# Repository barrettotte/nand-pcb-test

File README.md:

# nand-pcb-test

Homemade PCB test using a CNC router.

Hopefully this is useful to someone else wanting a single place to see the whole CNC PCB building process.
These notes assume you have a basic understanding of Kicad and Candle (grblcontrol).

## Why?

There are plenty of companies that offer cheap PCB manufacturing, but I'm impatient and bad at designing things correctly on the first try.
Imagine ordering a PCB, waiting a few days, and figuring out you messed up your design.
Manufacturing with a CNC router helps to eliminate waiting time between idea and implementation.

Alternatively, plenty of people use the chemical etching process (example: thermal transfer paper and ferric chloride) to build their PCBs.
I just don't have a good workspace to mess with nasty chemicals, so the CNC approach is more doable for me.
Maybe I'll also add a chemical etching bonus section in the future.

For 2+ sided PCBs, it would be worth ordering from a company. Double-sided PCBs are possible, but I have not attempted this yet.
I also haven't tried designs with SMD components yet, so that may also be a pain point that warrants ordering PCBs from a company.

## Equipment

- [Genmitsu 3020-PRO MAX V2 CNC Router](https://www.sainsmart.com/collections/new-genmitsu-collection/products/3020-pro-max-v2)
  - [3040 Y-Axis Extension Kit](https://www.sainsmart.com/collections/genmitsu-cnc-replacement-upgrade-parts/products/3020-yaxis-extension-kit) (optional)
- [FR-4 Copper Clad PCB Laminate Board, Single Side, 4 x 2.7 inch (10 piece)](https://www.amazon.com/dp/B01MCVLDDZ)
- Bits
  - [0.5mm PCB End Mill Bit](https://www.amazon.com/gp/product/B073RJ3SYZ)
  - [0.8mm PCB Drill Bit](https://www.amazon.com/gp/product/B091FD44Y3)
  - [2.5mm End Mill Bit](https://www.amazon.com/gp/product/B07P84V888)
  - [Assorted PCB Drill Bit Set](https://www.amazon.com/gp/product/B08M5PLF48)
- [Mini Dry Iron](https://www.amazon.com/gp/product/B09YXVWSTQ)
- [Thermal Transfer Paper](https://www.amazon.com/gp/product/B07GLGL2CX)
- [Monochrome Laser Printer](https://www.amazon.com/gp/product/B00NQ1CLTI)
- [Mini Drill Press](https://www.amazon.com/gp/product/B0BKZRD2P7)

## Build Process

### Circuit Design and Prototyping

- Design circuit in Kicad Schematic Editor
- Breadboard implementation
- Protoboard implementation (optional)
- Kicad Schematic Editor
  - Inspect > Electrical Rules Checker
  - Tools > Annotate Schematic
  - Tools > Assign Footprints
  - File > Plot > PDF, Plot All Pages

### PCB Design

- Open Kicad PCB Editor (or from Kicad Schematic Editor: Tools > Update PCB From Schematic)
- Generally only use back copper and front silkscreen
- Rearrange rats nest of components to eliminate overlap
- Set design rules (File > Board Setup)
  - Minimum clearance: 0.5mm
  - Minimum track width: 0.5mm
  - Copper to hole clearance: 0.5mm
  - Copper to edge clearance: 0.5mm
  - Minimum through hole: 0.7mm
  - Hole to hole clearance: 0.5mm
- Route tracks on `B.Cu` (back copper) layer. Ignore ground pins, will be filled later
- Select `Edge.Cuts` layer, draw a rectangle to trace board boundary, thickness 1mm
- Select `B.Cu` layer and add fill for ground
- Right click fill edge, Zones > Fill Zone
- Add orthogonal dimensions to `User.Drawings` layer to double check board width/height
- Place origin at top left of board
- Run Design Rules Checker
- If exporting `F.Silkscreen`, I recommend setting text thickness to 0.1mm 
- Export Gerber files (File > Plot)
  - Check Use drill/place file origin
  - Export `B.Cu`, `Edge.Cuts` (used in router step)
  - Export `B.Mask` (used in solder masking step) as PDF
  - Generate Drill Files (`*-NPTH.drl` and `*-PTH.drl`)
    - Drill Origin = Drill/place file origin
    - Drill Units = Millimeters
- Print (File > Print) `F.Silkscreen` and `F.Mask` layers to PDF (used in silkscreen step)
  - Verify Print One Page Per Layer is unchecked
  - Scale 1:1
  - Select Print Mirrored

### Bits

Refer to bits listed in Equipment section above.

- Isolation routing: 0.5mm pcb milling bit
- Holes: 0.8mm drill bit
- Edge cut: 2.5mm end mill bit

I know a lot of people seem to recommend v-bits, but I found them to cut too
inconsistent to quickly throw together boards. 

I did manage to get a couple boards cut with a 0.1mm 60deg bit after manually offsetting my heightmap by 0.05 increments, but I could not replicate this every time. 
Switching to the pcb milling bit removed ~5-10 minutes of manual adjustment.

### Computer Aided Manufacturing (CAM)

- Launch FlatCAM
- Load `B.Cu` and `Edge.Cuts` gerber files (File > Open Gerber)
- Add drill files (`*.drl`) (File > Open Excellon)
  - Note: Ignore "No geometry found in file" error if no NPTH holes needed
- Options tab
  - Set units to mm
- Mirror on y-axis since we're cutting the back copper
  - Tool > Double-Sided PCB Tool
  - Mirror `B.Cu` and `*.drl` files on y-axis using Point/Box
- Select `*-B_Cu.gbr`
  - Isolation Routing section
  - Tool dia: 0.45 (note: 0.05 less than clearance set in Kicad)
  - Width (# passes): 2
  - Pass overlap: 0.10
  - Combine Passes: yes
  - Click Generate Geometry
- Select `*-B_Cu.gbr_iso`
  - Create CNC Job section
  - Cut Z: -0.015
  - Travel Z: 2
  - Feed Rate: 85.0
  - Tool dia: 0.45 (note: 0.05 less than clearance set in Kicad)
  - Spindle speed: 10000
  - Multi-Depth: yes
  - Depth/Pass: 0.08
  - Click Generate
- Select `*-B_Cu.gbr_iso_cnc`, export G-Code to `B_Cu.nc`
- Select `*-PTH.drl`
  - If too many sizes of drills, go back to Kicad and change hole sizes of individual components (we can always redrill by hand later if holes too small)
  - Create CNC Job section
  - Cut Z: -2
  - Travel Z: 2
  - Feed Rate: 100.0
  - Tool Change: no (unless using multiple drill sizes)
  - Spindle Speed: 10000
  - Click Generate
- Select `*-PTH.drl_cnc`, set tool dia to 0.8, export G-Code to `PTH.drl.nc`
- Select `*.Edge_Cuts.gbr`
  - Board cutout section
  - Tool dia: 2.5
  - Margin: 0.1
  - Gap size: 1.0
  - Gaps: 4
  - Click Generate Geometry
- Select `*-Edge_Cuts.gbr_cutout`
  - Create CNC Job section
  - Cut Z: -2
  - Travel Z: 2.0
  - Feed Rate: 50.0
  - Tool dia: 2.5
  - Spindle speed: 10000
  - Multi-Depth: yes
  - Depth/pass: 0.25
  - Click Generate
- Select `*-Edge_Cuts.gbr_cutout_cnc`, export G-Code to `Edge_Cuts.nc`

### Preparing Silkscreen

- Open `F.Silkscreen` PDF in Inkscape (to remove blank space of PDF document)
  - Select silkscreen components, export
  - Export Selection tab, Export Selected Only, 300.0 DPI, SVG

### CNC Routing

Refer to bits in "Computer Aided Manufacturing (CAM)" section

To secure the PCB to the bed, 
I used 3D printed M6 Plate Clamps from https://www.printables.com/model/250450-enhancements-for-sainsmartgenmitsu-3020-pro-max-cn/files. 
Alternatively, I saw a lot of people using carpet tape.

Probe setup using aluminum tape and z-probe that came with CNC router.

- Jog machine to upper left corner, z probe, zero XY
- Height map
  - Load nc file, click auto
  - Zero XYZ, set bit at origin
  - Probe grid, set to be ~10mm apart
  - Interpolation grid: 20, 20
  - zt = 1.0, zb = -1.0
  - Click Probe
  - Save as `height.map`
  - Click edit mode to leave edit mode
  - Verify use heightmap is checked
- Remove probes
- Load `B.Cu.nc`
- Swap to drill bit, re-zero Z
- Load `PTH.drl.nc`
- Swap to edge cut bit, re-zero Z
- Load `Edge_Cuts.nc`

### Silkscreen

- Load thermal transfer paper into printer
- Print `F.Silkscreen` SVG onto thermal transfer paper (smooth side up)
  - Ensure scale is 100%
- Tape thermal paper to front of PCB (toner side down)
- Use highest setting of dry iron to heat evenly for 2-3 minutes
- Apply polycrylic to preserve silkscreen

### Final Steps

- Use mini drill press to adjust any holes for larger through hole parts
- Use 400-600 grit sandpaper and/or steel wool to remove any small burrs on back copper
- File down tabs on sides of PCB
- Clean off with a bit of isopropyl alcohol
- Use multimeter to check all tracks for shorts
- Solder components
- Clean off any flux with isopropyl

## Archive

I tried to do a couple different steps that I hope to try again in the future.
I left my notes in [archive/](archive/).

## References

- [Candle](https://github.com/trasz/grblControl)
- [FlatCAM](http://flatcam.org/)
- [GCODE Reference](https://marlinfw.org/meta/gcode/)
- Youtube
  - [Homemade custom PCB guide using free KiCAD software; Teaching Tech](https://www.youtube.com/watch?v=NgDXPWaA5Ic)
  - [Homemade PCB using thermal transfer paper](https://www.youtube.com/watch?v=aemG_4sDz_Q)
  - [Intro to Kicad; Shawn Hymel](https://www.youtube.com/playlist?list=PL3bNyZYHcRSUhUXUt51W6nKvxx2ORvUQB)
  - [Machining a PCB on the 3-axis CNC Bridgeport Mill; Usagi Electric](https://www.youtube.com/watch?v=AB84_vbH_e8)
  - [Milling PCBs on a Homemade CNC (Part 2): Masking](https://www.youtube.com/watch?v=qIxvXU7KDmE)
  - [Milling Printed Circuit Boards (PCBs) on a Cheap CNC Machine; Matt's Electronics & RC](https://www.youtube.com/watch?v=bQ6_oYZrsjk)
  - [Relay Calculators: Episode 8 - Using FlatCAM and a CNC mill to make PCBs; Usagi Electric](https://www.youtube.com/watch?v=F2FRN5z2S78)
  - [Sainsmart Genmitsu 3020 Pro Max - 300W Spindle & Linear Rails - Build, Test & Review; techydiy](https://www.youtube.com/watch?v=5vaAthrJQm0)

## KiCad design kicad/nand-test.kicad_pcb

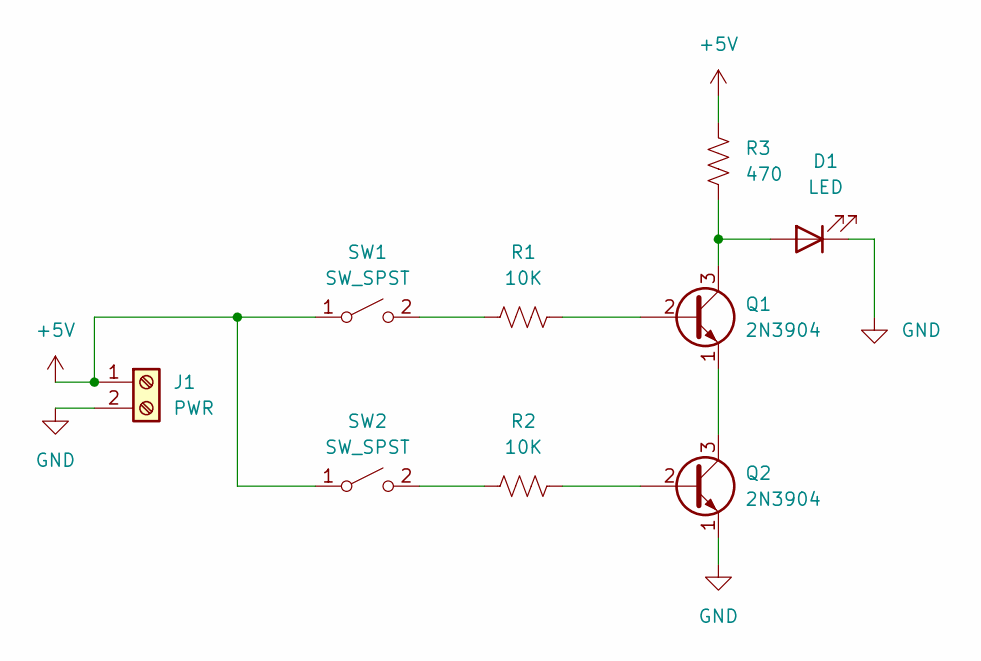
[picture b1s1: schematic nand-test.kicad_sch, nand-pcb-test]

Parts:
D1: LED; LED_D5.0mm
J1: PWR; TerminalBlock_Altech_AK300-2_P5.00mm
Q1, Q2: 2N3904; TO-92_Inline
R1, R2: 10K; R_Axial_DIN0207_L6.3mm_D2.5mm_P10.16mm_Horizontal
R3: 470; R_Axial_DIN0207_L6.3mm_D2.5mm_P10.16mm_Horizontal
SW1, SW2: SW_SPST; SW_PUSH_6mm

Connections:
+5V: J1.1, R3.1, SW1.1 (A), SW2.1 (A)
GND: D1.1 (K), J1.2, Q2.1 (E)
unnamed: D1.2 (A), Q1.3 (C), R3.2
unnamed: Q1.1 (E), Q2.3 (C)
unnamed: Q1.2 (B), R1.2
unnamed: Q2.2 (B), R2.2
unnamed: R1.1, SW1.2 (B)
unnamed: R2.1, SW2.2 (B)

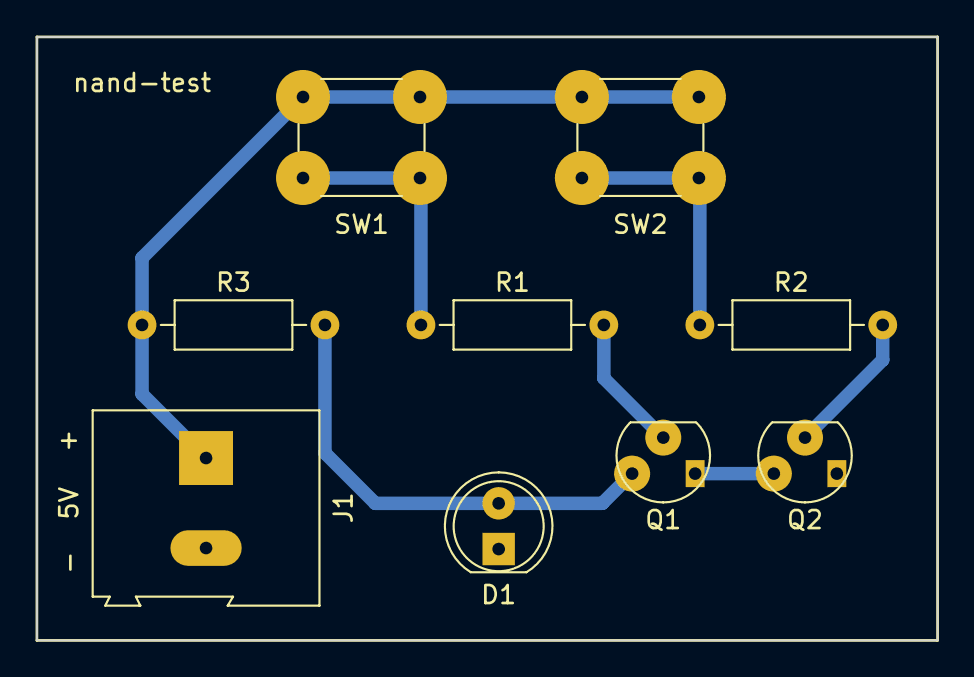
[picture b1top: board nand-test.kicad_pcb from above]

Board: 2 copper layers, 50.0 x 33.5 mm, 9 parts (0 on the bottom side), 8 nets.

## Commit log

2024-02-28 base writeup and kicad pcb
2024-02-28 adds gitattributes
2024-02-28 adds .gitattributes
2024-03-03 generated gerber and gcode
2024-03-08 updates gerber/gcode files
2024-03-09 update gerber and gcode
2024-03-09 updates gcode
2024-03-18 updates gerbers, gcode, and notes
2024-03-31 archives laser silkscreen steps
2024-03-31 adds images
2024-03-31 adds silkscreen steps
2024-04-02 add images
2024-04-02 archive solder mask steps
2024-04-03 adds assembled PCB images
